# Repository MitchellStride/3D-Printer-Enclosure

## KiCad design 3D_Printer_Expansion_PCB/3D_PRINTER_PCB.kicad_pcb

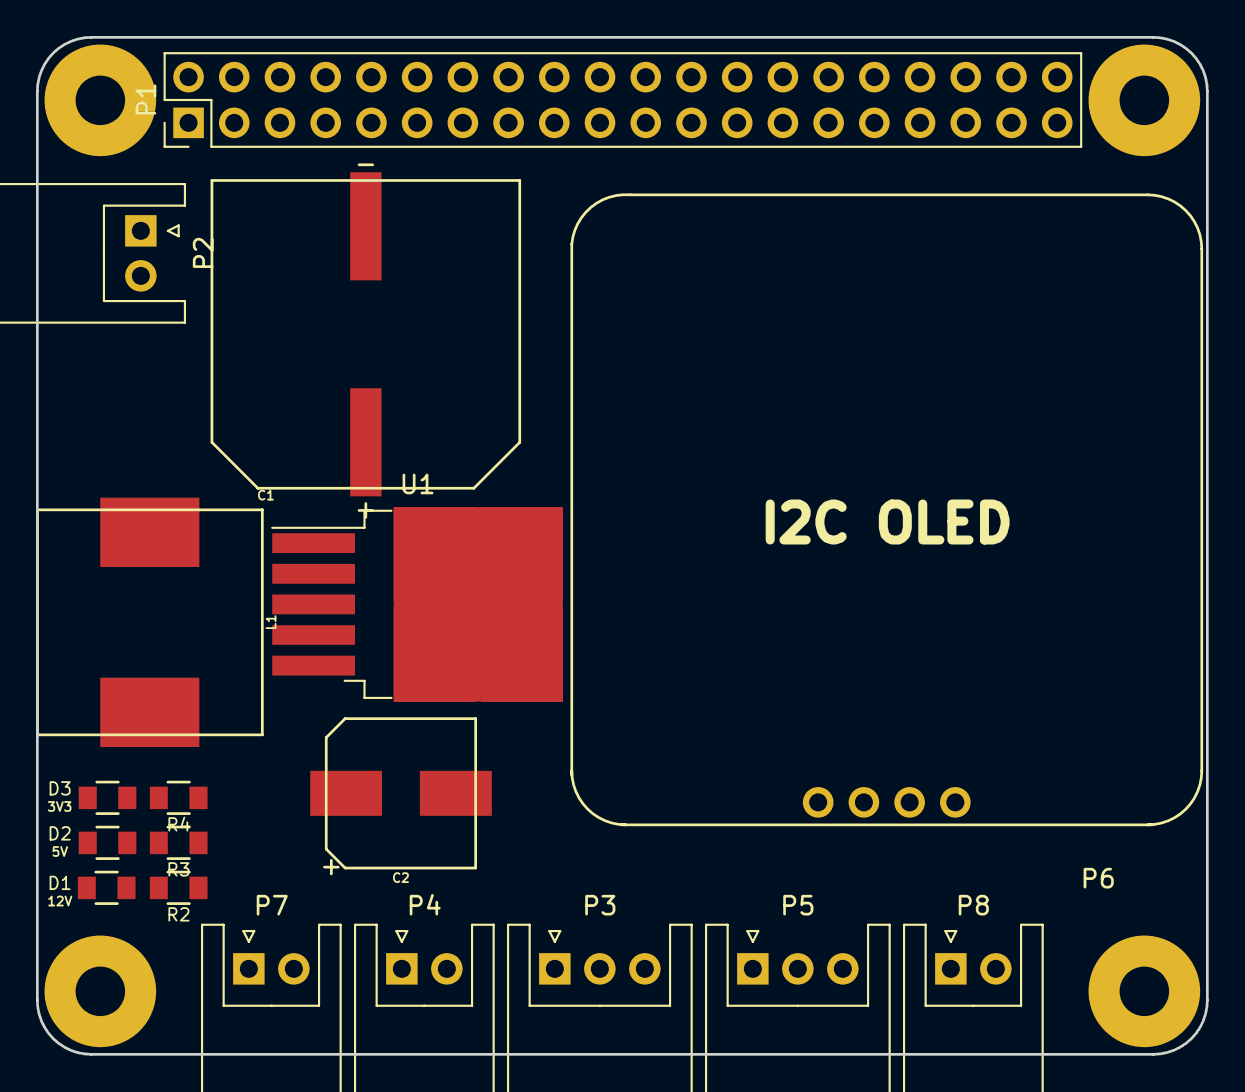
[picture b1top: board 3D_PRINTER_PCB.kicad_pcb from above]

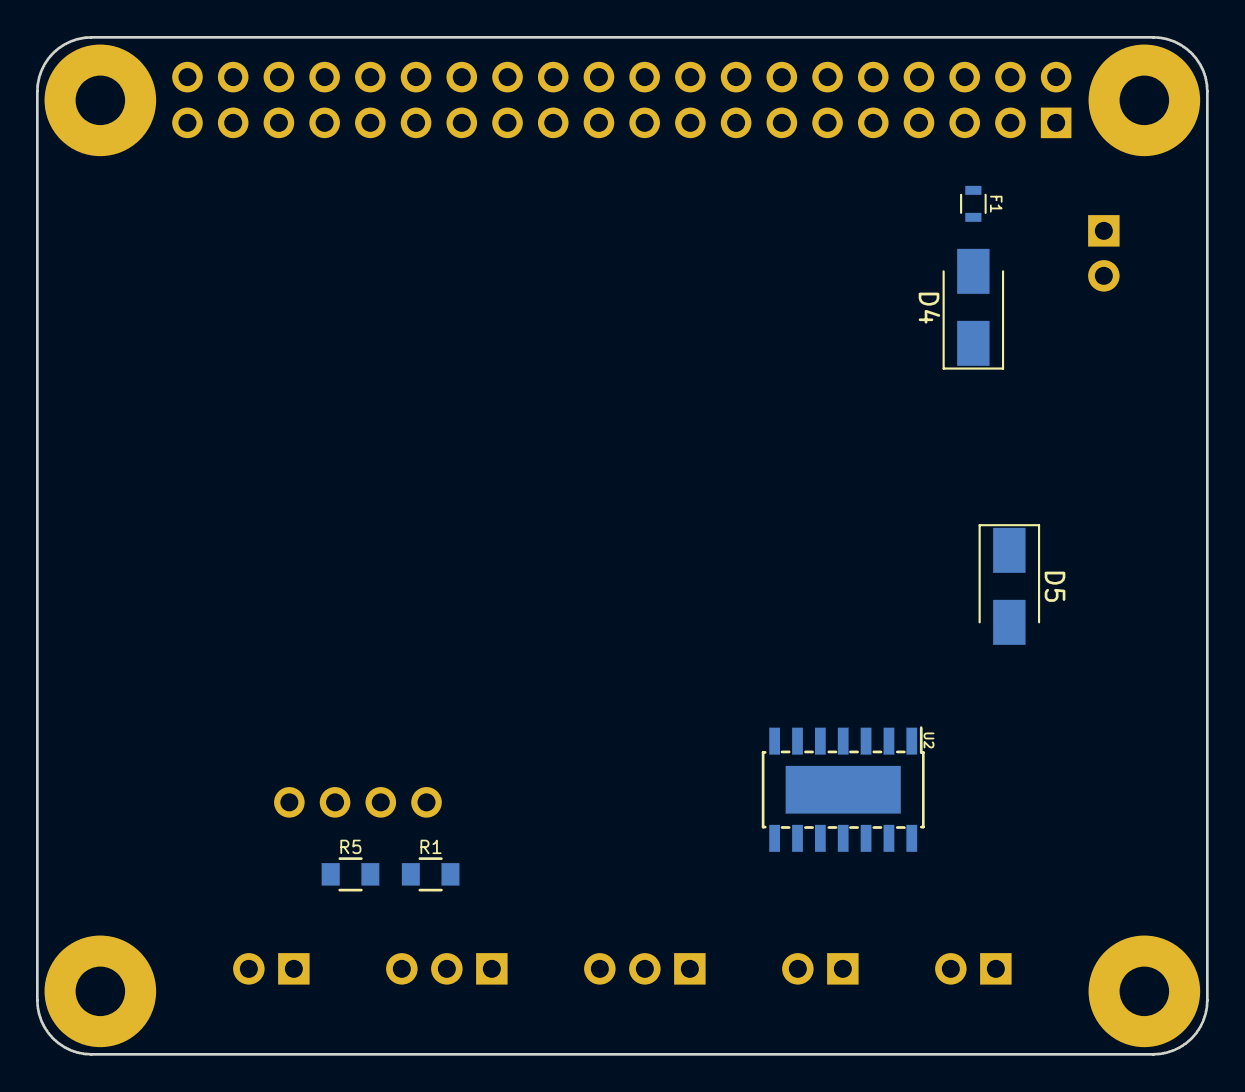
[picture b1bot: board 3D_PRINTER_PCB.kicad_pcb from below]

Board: 2 copper layers, 65.0 x 56.5 mm, 28 parts (6 on the bottom side), 19 nets, no tracks yet.

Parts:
C1: 680uF; C_Nichicon_UCZ_D16_H17
C2: 220uF; C_Nichicon_ULH_D8_H11
D1: 12V; SMD_pkg_0805
D2: 5V; SMD_pkg_0805
D3: 3V3; SMD_pkg_0805
D4, D5: 30V 3A; D_SMA
F1: 3A; SMD_pkg_0603
L1: 33uH; L_Eaton_DR124
M1, M2, M3, M4: Mount; M2.5_MountingHole
P1: RPi3; Pin_Header_Straight_2x20_Pitch2.54mm
P2: PWR; JST_XH_S02B-XH-A_02x2.50mm_Angled
P3: SERVO; JST_XH_S03B-XH-A_03x2.50mm_Angled
P4: FAN; JST_XH_S02B-XH-A_02x2.50mm_Angled
P5: TEMP; JST_XH_S03B-XH-A_03x2.50mm_Angled
P6: OLED; I2C_OLED
P7: LIGHT; JST_XH_S02B-XH-A_02x2.50mm_Angled
P8: DOOR; JST_XH_S02B-XH-A_02x2.50mm_Angled
R1: 4k7; SMD_pkg_0805
R2: 2k; SMD_pkg_0805
R3: 620; SMD_pkg_0805
R4: 270; SMD_pkg_0805
R5: 10k; SMD_pkg_0805
U1: LM2596S-5; TO-263-5_TabPin3
U2: BTS50302; SOIC-14_N-TAB

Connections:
+3.3V: D3.2, P1.1, P1.17, P5.3, R1.1, R5.2
+5V: C2.1, D2.2, L1.2, P1.2, P1.4, P3.2, P6.1, U1.4
+12V: D1.2, F1.1, P2.1, U2.TAB
/FAN_CTRL: P4.1, U2.12, U2.13, U2.14
/GPIO4: P1.7, P5.2, R1.2
/GPIO14: P1.8, U2.2
/GPIO15: P1.10, U2.6
/GPIO17: P1.11, P8.1, R5.1
/GPIO18: P1.12, P3.3
/I2C_SCL: P1.5, P6.3
/I2C_SDA: P1.3, P6.4
/LIGHT_CTRL: P7.1, U2.8, U2.9, U2.10
GND: C1.2, C2.2, D5.2, P1.6, P1.9, P1.14, P1.20, P1.25, P1.30, P1.34, P1.39, P2.2, P3.1, P4.2, P5.1, P6.2, P7.2, P8.2, R2.1, R3.1, R4.1, U1.3, U1.5, U2.1
unnamed: C1.1, D4.1, U1.1
unnamed: D1.1, R2.2
unnamed: D2.1, R3.2
unnamed: D3.1, R4.2
unnamed: D4.2, F1.2
unnamed: D5.1, L1.1, U1.2

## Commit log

2018-03-30 added corner bracket
2019-11-22 alienware push
